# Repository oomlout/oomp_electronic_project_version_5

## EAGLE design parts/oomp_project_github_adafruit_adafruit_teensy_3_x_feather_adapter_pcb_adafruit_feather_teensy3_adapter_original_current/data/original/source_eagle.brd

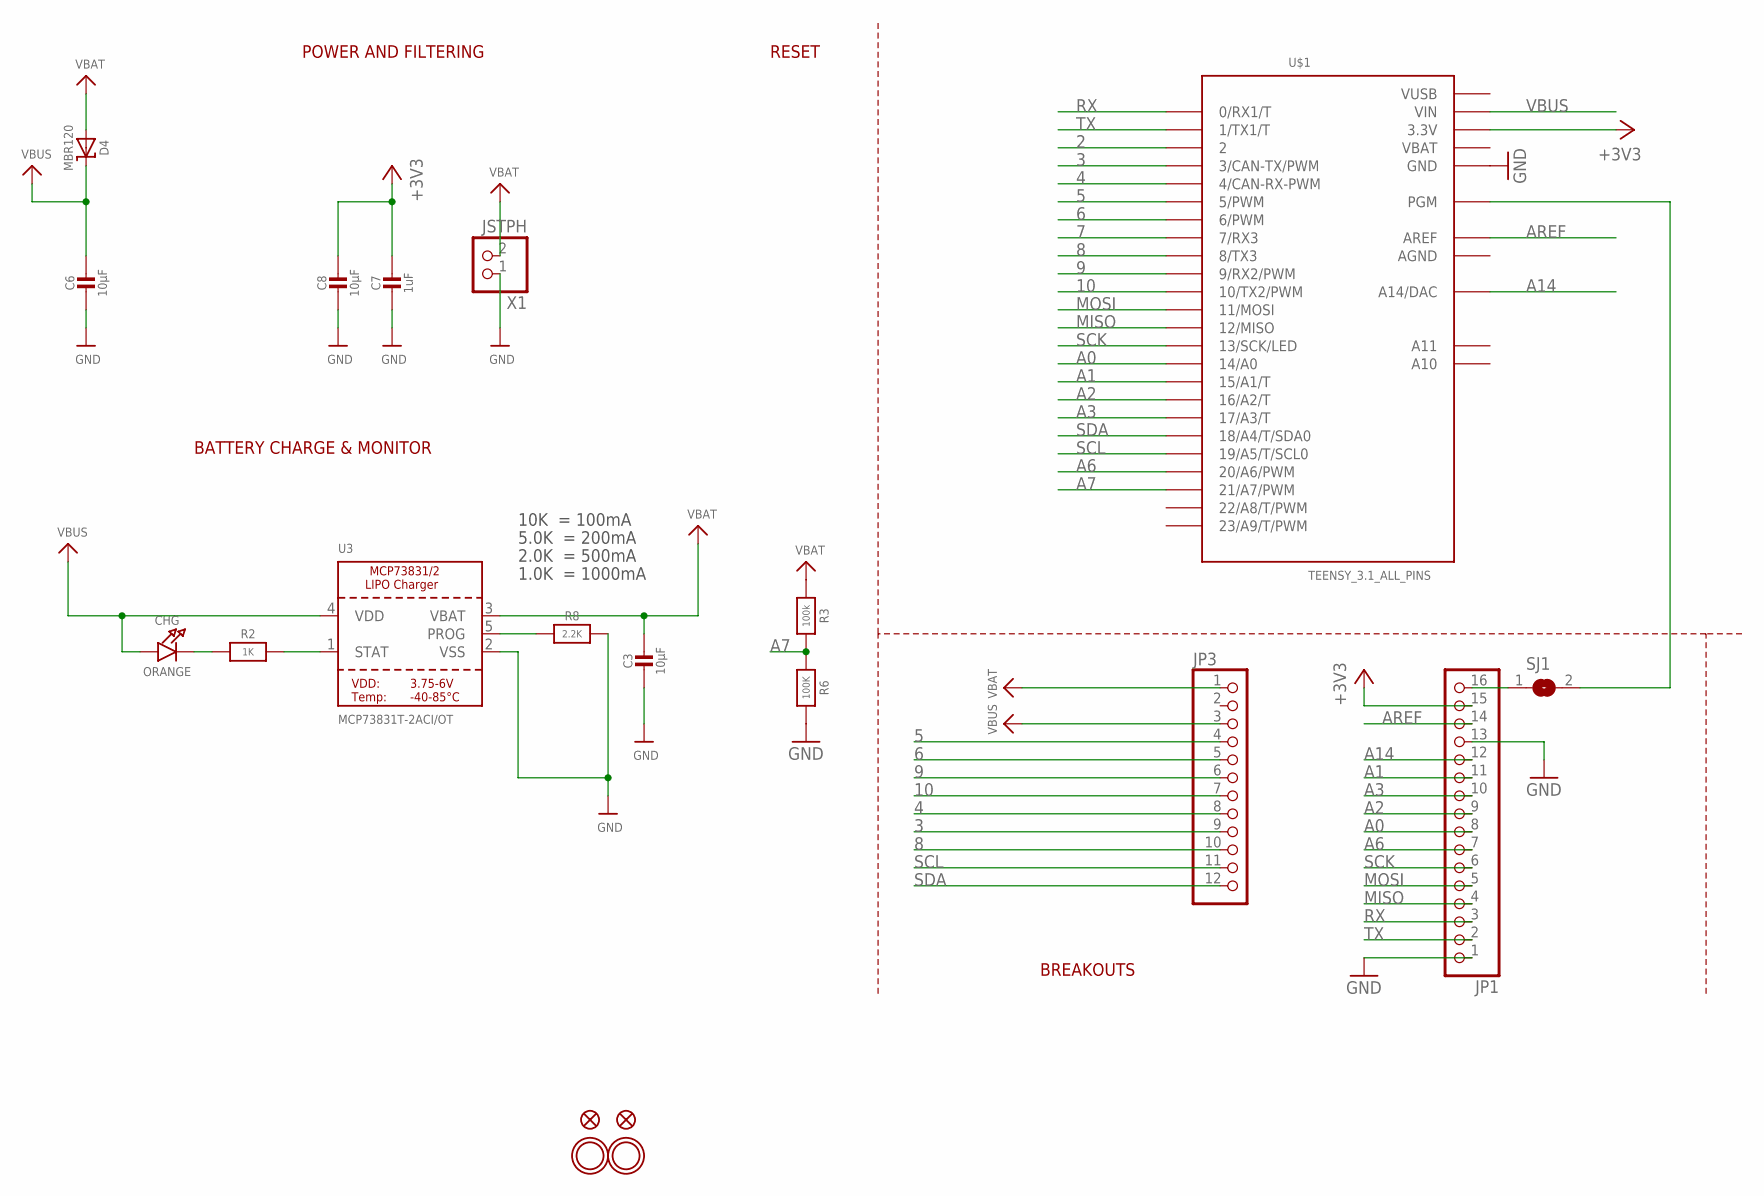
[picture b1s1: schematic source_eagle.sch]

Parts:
C3, C6, C8: 10µF; 0805-NO
C7: 1uF; 0603-NO
CHG: ORANGE; CHIPLED_0805_NOOUTLINE
D4: MBR120; SOD-123
JP1: HEADER-1X16ROUND; 1X16_ROUND
JP3: HEADER-1X12; 1X12_ROUND
R2: 1K; 0603-NO
R3: 100k; 0603-NO
R6: 100K; 0603-NO
R8: 2.2K; 0603-NO
SJ1: SOLDERJUMPERCLOSED; SOLDERJUMPER_CLOSEDWIRE
U3: MCP73831T-2ACI/OT; SOT23-5
U$1: TEENSY_3.1_ALL_PINS; TEENSY3-ALL_PINS
U$31, U$32: MOUNTINGHOLE2.5; MOUNTINGHOLE_2.5_PLATED
U$34, U$35: FIDUCIAL""; FIDUCIAL_1MM
X1: JSTPH; JSTPH2

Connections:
2: U$1.2
3: JP3.9, U$1.3 (3/CAN-TX/PWM)
4: JP3.8, U$1.4 (4/CAN-RX-PWM)
5: JP3.4, U$1.5 (5/PWM)
6: JP3.5, U$1.6 (6/PWM)
7: U$1.7 (7/RX3)
8: JP3.10, U$1.8 (8/TX3)
9: JP3.6, U$1.9 (9/RX2/PWM)
10: JP3.7, U$1.10 (10/TX2/PWM)
+3V3: C7.1, C8.1, JP1.15, U$1.3.3V, U$1.3.3V1 (3.3V)
A0: JP1.8, U$1.14/A0
A1: JP1.11, U$1.15/A1 (15/A1/T)
A2: JP1.9, U$1.16/A2 (16/A2/T)
A3: JP1.10, U$1.17/A3 (17/A3/T)
A6: JP1.7, U$1.20/A6 (20/A6/PWM)
A7: R3.2, R6.1, U$1.21/A7 (21/A7/PWM)
A14: JP1.12, U$1.RESET/DAC (A14/DAC)
AGND: U$1.AGND
AREF: JP1.14, U$1.AREF
BOOT: SJ1.2, U$1.PGM
GND: C3.2, C6.2, C7.2, C8.2, JP1.1, JP1.13, R6.2, R8.2, U3.2 (VSS), U$1.GND, U$1.GND1 (GND), X1.1
MISO: JP1.4, U$1.12 (12/MISO)
MOSI: JP1.5, U$1.11 (11/MOSI)
unnamed: CHG.C, R2.1
unnamed: R2.2, U3.1 (STAT)
unnamed: R8.1, U3.5 (PROG)
RST/BOOT: JP1.16, SJ1.1
RX: JP1.3, U$1.0 (0/RX1/T)
SCK: JP1.6, U$1.13 (13/SCK/LED)
SCL: JP3.11, U$1.19/A5 (19/A5/T/SCL0)
SDA: JP3.12, U$1.18/A4 (18/A4/T/SDA0)
TX: JP1.2, U$1.1 (1/TX1/T)
VBAT: C3.1, D4.A, JP3.1, R3.1, U3.3 (VBAT), U$1.VBAT, X1.2
VBUS: C6.1, CHG.A, D4.C, JP3.3, U3.4 (VDD), U$1.VIN
VUSB: U$1.VUSB

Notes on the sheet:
POWER AND FILTERING
RESET
10K = 100mA
5.0K = 200mA
2.0K = 500mA
1.0K = 1000mA
BATTERY CHARGE & MONITOR
BREAKOUTS

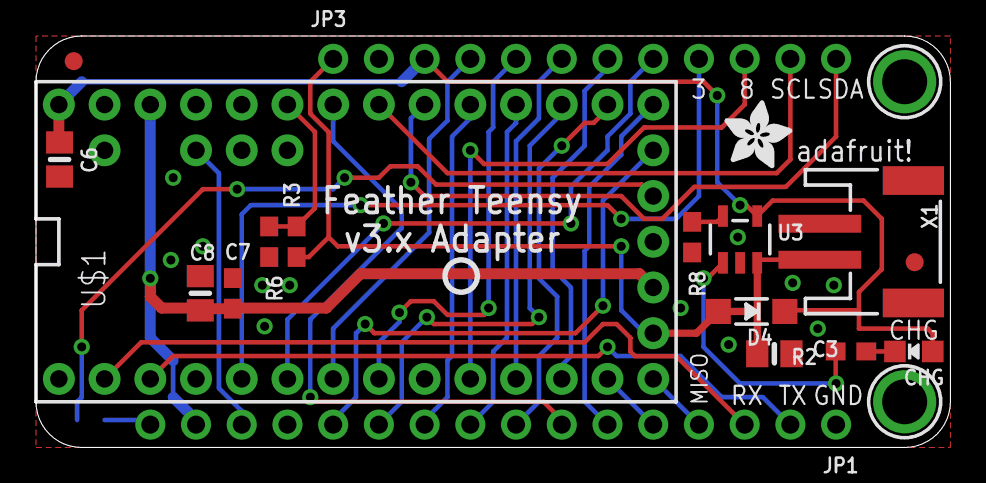
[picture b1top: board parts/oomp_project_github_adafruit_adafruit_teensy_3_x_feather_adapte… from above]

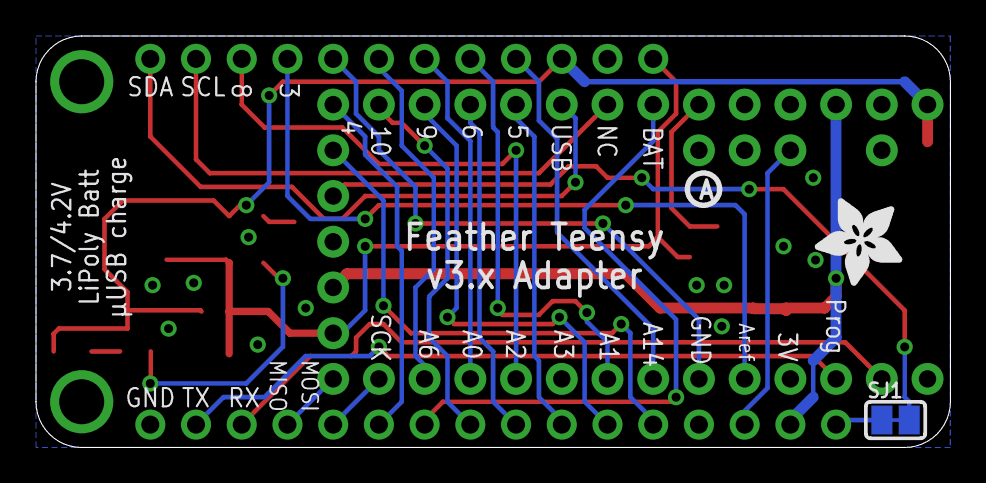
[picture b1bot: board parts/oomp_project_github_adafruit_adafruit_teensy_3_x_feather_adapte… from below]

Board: 2 copper layers, 50.8 x 22.9 mm, 24 parts (3 on the bottom side), 31 nets.

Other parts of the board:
U$4: ADAFRUIT_5MM
U$5, U$6: PCBFEAT-REV-040
U$7: ADAFRUIT_3.5MM

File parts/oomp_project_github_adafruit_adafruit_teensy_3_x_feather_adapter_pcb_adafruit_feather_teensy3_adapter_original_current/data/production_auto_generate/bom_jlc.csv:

Comment,Designator,Footprint,LCSC Part #
,JP3,Adafruit Feather Teensy3 Adapter Original-import-fps:1X12_ROUND,C7501588
,JP1,Adafruit Feather Teensy3 Adapter Original-import-fps:1X16_ROUND,C7501270
,U$7,Adafruit Feather Teensy3 Adapter Original-import-fps:ADAFRUIT_3.5MM,
,U$4,Adafruit Feather Teensy3 Adapter Original-import-fps:ADAFRUIT_5MM,
,"U$5,U$6",Adafruit Feather Teensy3 Adapter Original-import-fps:PCBFEAT-REV-040,
100k,R3,Adafruit Feather Teensy3 Adapter Original-import-fps:0603-NO,C25803
100K,R6,Adafruit Feather Teensy3 Adapter Original-import-fps:0603-NO,C25803
10µF,"C3,C6,C8",Adafruit Feather Teensy3 Adapter Original-import-fps:0805-NO,
1K,R2,Adafruit Feather Teensy3 Adapter Original-import-fps:0603-NO,C2907002
1uF,C7,Adafruit Feather Teensy3 Adapter Original-import-fps:0603-NO,C5673
2.2K,R8,Adafruit Feather Teensy3 Adapter Original-import-fps:0603-NO,C4190
"FIDUCIAL""""","U$34,U$35",Adafruit Feather Teensy3 Adapter Original-import-fps:FIDUCIAL_1MM,
JSTPH,X1,Adafruit Feather Teensy3 Adapter Original-import-fps:JSTPH2,
MBR120,D4,Adafruit Feather Teensy3 Adapter Original-import-fps:SOD-123,
MCP73831T-2ACI/OT,U3,Adafruit Feather Teensy3 Adapter Original-import-fps:SOT23-5,
ORANGE,CHG0,Adafruit Feather Teensy3 Adapter Original-import-fps:CHIPLED_0805_NOOUTLINE,
TEENSY_3.1_ALL_PINS,U$1,Adafruit Feather Teensy3 Adapter Original-import-fps:TEENSY3-ALL_PINS,

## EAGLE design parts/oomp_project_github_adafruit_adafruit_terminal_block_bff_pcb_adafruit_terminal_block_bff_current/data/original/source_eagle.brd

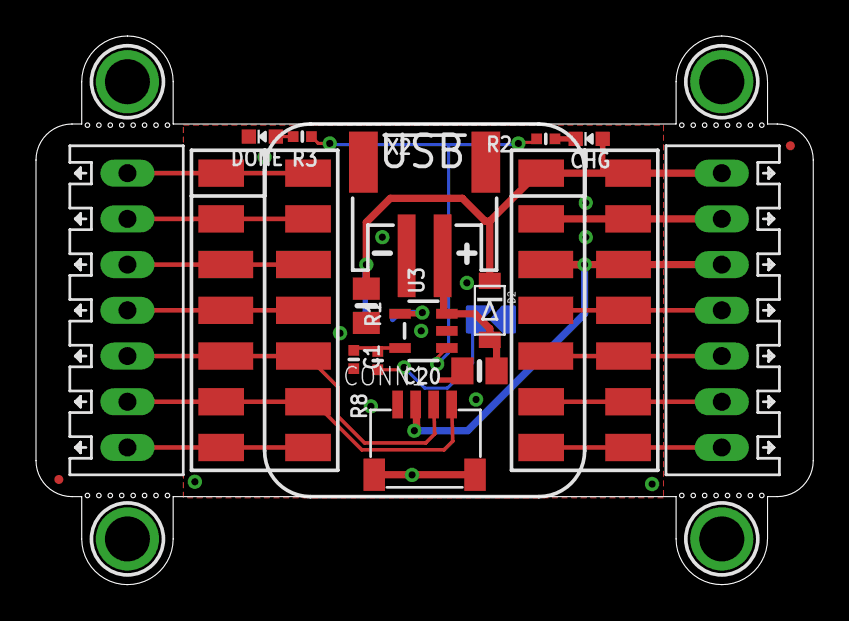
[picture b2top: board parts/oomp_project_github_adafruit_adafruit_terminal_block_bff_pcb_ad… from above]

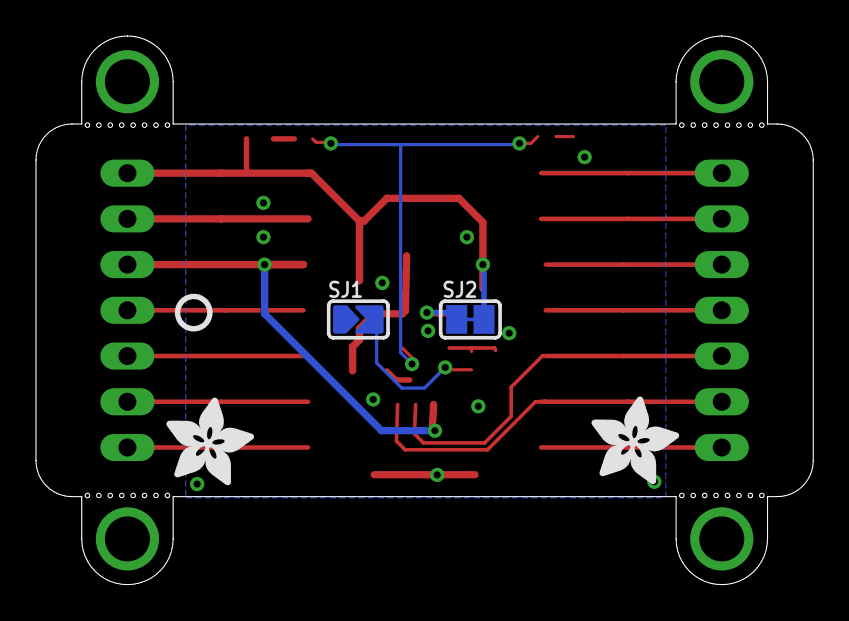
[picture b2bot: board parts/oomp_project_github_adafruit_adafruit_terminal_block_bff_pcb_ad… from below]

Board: 2 copper layers, 43.2 x 30.5 mm, 64 parts (26 on the bottom side), 21 nets.

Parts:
C1, C20: 10uF; 0805-NO
CHG: ORANGE; CHIPLED_0603_NOOUTLINE
CONN1: STEMMA_I2C_QT; JST_SH4
D2: PMEG2020; SOD-123FL
DONE: GREEN; CHIPLED_0603_NOOUTLINE
FID1, FID2: FIDUCIAL_0.5MM
JP1, JP2: Terminal; 1X07_2.54MMTERMINAL
PLABEL0: PLABEL0
PLABEL1: PLABEL1
PLABEL2: PLABEL2
PLABEL3: PLABEL3
PLABEL4: PLABEL4
PLABEL5: PLABEL5
PLABEL6: PLABEL6
PLABEL7: PLABEL7
PLABEL8: PLABEL8
PLABEL9: PLABEL9
PLABEL10: PLABEL10
PLABEL11: PLABEL11
PLABEL12: PLABEL12
PLABEL13: PLABEL13
PLABEL14: PLABEL14
PLABEL15: PLABEL15
PLABEL16: PLABEL16
PLABEL17: PLABEL17
PLABEL18: PLABEL18
PLABEL19: PLABEL19
PLABEL20: PLABEL20
PLABEL21: PLABEL21
PLABEL22: PLABEL22
PLABEL23: PLABEL23
PLABEL24: PLABEL24
PLABEL25: PLABEL25
PLABEL26: PLABEL26
PLABEL27: PLABEL27
PLABEL28: PLABEL28
PLABEL29: PLABEL29
PLABEL31: PLABEL31
PLABEL32: PLABEL32
PLABEL33: PLABEL33
PLABEL34: PLABEL34
PLABEL35: PLABEL35
PLABEL36: PLABEL36
PLABEL37: PLABEL37
PLABEL38: PLABEL38
R1, R2, R3, R8: 5.1K; _0402NO
SJ1: SOLDERJUMPER_ARROW_NOPASTE
SJ2: SOLDERJUMPER_CLOSEDWIRE
U3: MCP73831T-2ACI/OT; SOT23-5
U$1, U$2, U$3, U$4: MOUNTINGHOLE2.5; MOUNTINGHOLE_2.5_PLATED
U$7, U$8: ADAFRUIT_5MM
U$9: PCBFEAT-REV-040
X1: QTPY_SOCKET_DUAL_SMT; QTPY_SMT
X2: JSTPH; JSTPH2_BATT

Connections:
3.3V: CONN1.2, JP1.5, X1.12, X1.12B
+5V: C1.1, CHG.A, D2.C, JP1.7, SJ2.2, X1.14, X1.14B
A0: JP2.1, X1.1, X1.1B
A1: JP2.2, X1.2, X1.2B
A2: JP2.3, X1.3, X1.3B
A3: JP2.4, X1.4, X1.4B
GND: C1.2, C20.2, CONN1.1, CONN1.MT1, CONN1.MT2, DONE.C, JP1.6, R8.2, SJ1.1, U3.2, X1.13, X1.13B, X2.1, X2.NC1, X2.NC2
MISO: JP1.3, X1.10, X1.10B
MOSI: JP1.4, X1.11, X1.11B
unnamed: R1.1, SJ1.2
unnamed: CHG.C, R2.1
unnamed: R2.2, R3.1, U3.1
unnamed: R1.2, R8.1, U3.5
unnamed: DONE.A, R3.2
unnamed: SJ2.1, U3.4
RX: JP1.1, X1.8, X1.8B
SCK: JP1.2, X1.9, X1.9B
SCL: CONN1.4, JP2.6, X1.6, X1.6B
SDA: CONN1.3, JP2.5, X1.5, X1.5B
TX: JP2.7, X1.7, X1.7B
VBAT: C20.1, D2.A, U3.3, X2.2

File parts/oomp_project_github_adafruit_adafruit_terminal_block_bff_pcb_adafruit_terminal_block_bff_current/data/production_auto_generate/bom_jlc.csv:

Comment,Designator,Footprint,LCSC Part #
,"U$7,U$8",Adafruit Terminal Block BFF-import-fps:ADAFRUIT_5MM,
,U$9,Adafruit Terminal Block BFF-import-fps:PCBFEAT-REV-040,
,PLABEL0,Adafruit Terminal Block BFF-import-fps:PLABEL0,
,PLABEL1,Adafruit Terminal Block BFF-import-fps:PLABEL1,
,PLABEL10,Adafruit Terminal Block BFF-import-fps:PLABEL10,
,PLABEL11,Adafruit Terminal Block BFF-import-fps:PLABEL11,
,PLABEL12,Adafruit Terminal Block BFF-import-fps:PLABEL12,
,PLABEL13,Adafruit Terminal Block BFF-import-fps:PLABEL13,
,PLABEL14,Adafruit Terminal Block BFF-import-fps:PLABEL14,
,PLABEL15,Adafruit Terminal Block BFF-import-fps:PLABEL15,
,PLABEL16,Adafruit Terminal Block BFF-import-fps:PLABEL16,
,PLABEL17,Adafruit Terminal Block BFF-import-fps:PLABEL17,
,PLABEL18,Adafruit Terminal Block BFF-import-fps:PLABEL18,
,PLABEL19,Adafruit Terminal Block BFF-import-fps:PLABEL19,
,PLABEL2,Adafruit Terminal Block BFF-import-fps:PLABEL2,
,PLABEL20,Adafruit Terminal Block BFF-import-fps:PLABEL20,
,PLABEL21,Adafruit Terminal Block BFF-import-fps:PLABEL21,
,PLABEL22,Adafruit Terminal Block BFF-import-fps:PLABEL22,
,PLABEL23,Adafruit Terminal Block BFF-import-fps:PLABEL23,
,PLABEL24,Adafruit Terminal Block BFF-import-fps:PLABEL24,
,PLABEL25,Adafruit Terminal Block BFF-import-fps:PLABEL25,
,PLABEL26,Adafruit Terminal Block BFF-import-fps:PLABEL26,
,PLABEL27,Adafruit Terminal Block BFF-import-fps:PLABEL27,
,PLABEL28,Adafruit Terminal Block BFF-import-fps:PLABEL28,
,PLABEL29,Adafruit Terminal Block BFF-import-fps:PLABEL29,
,PLABEL3,Adafruit Terminal Block BFF-import-fps:PLABEL3,
,PLABEL31,Adafruit Terminal Block BFF-import-fps:PLABEL31,
,PLABEL32,Adafruit Terminal Block BFF-import-fps:PLABEL32,
,PLABEL33,Adafruit Terminal Block BFF-import-fps:PLABEL33,
,PLABEL34,Adafruit Terminal Block BFF-import-fps:PLABEL34,
,PLABEL35,Adafruit Terminal Block BFF-import-fps:PLABEL35,
,PLABEL36,Adafruit Terminal Block BFF-import-fps:PLABEL36,
,PLABEL37,Adafruit Terminal Block BFF-import-fps:PLABEL37,
,PLABEL38,Adafruit Terminal Block BFF-import-fps:PLABEL38,
,PLABEL4,Adafruit Terminal Block BFF-import-fps:PLABEL4,
,PLABEL5,Adafruit Terminal Block BFF-import-fps:PLABEL5,
,PLABEL6,Adafruit Terminal Block BFF-import-fps:PLABEL6,
,PLABEL7,Adafruit Terminal Block BFF-import-fps:PLABEL7,
,PLABEL8,Adafruit Terminal Block BFF-import-fps:PLABEL8,
,PLABEL9,Adafruit Terminal Block BFF-import-fps:PLABEL9,
10uF,"C1,C20",Adafruit Terminal Block BFF-import-fps:0805-NO,
5.1K,"R1,R2,R3,R8",Adafruit Terminal Block BFF-import-fps:_0402NO,C25905
GREEN,DONE0,Adafruit Terminal Block BFF-import-fps:CHIPLED_0603_NOOUTLINE,
JSTPH,X2,Adafruit Terminal Block BFF-import-fps:JSTPH2_BATT,
MCP73831T-2ACI/OT,U3,Adafruit Terminal Block BFF-import-fps:SOT23-5,
ORANGE,CHG0,Adafruit Terminal Block BFF-import-fps:CHIPLED_0603_NOOUTLINE,
PMEG2020,D2,Adafruit Terminal Block BFF-import-fps:SOD-123FL,
QTPY_SOCKET_DUAL_SMT,X1,Adafruit Terminal Block BFF-import-fps:QTPY_SMT,
STEMMA_I2C_QT,CONN1,Adafruit Terminal Block BFF-import-fps:JST_SH4,C160404
Terminal,"JP1,JP2",Adafruit Terminal Block BFF-import-fps:1X07_2.54MMTERMINAL,C7501585

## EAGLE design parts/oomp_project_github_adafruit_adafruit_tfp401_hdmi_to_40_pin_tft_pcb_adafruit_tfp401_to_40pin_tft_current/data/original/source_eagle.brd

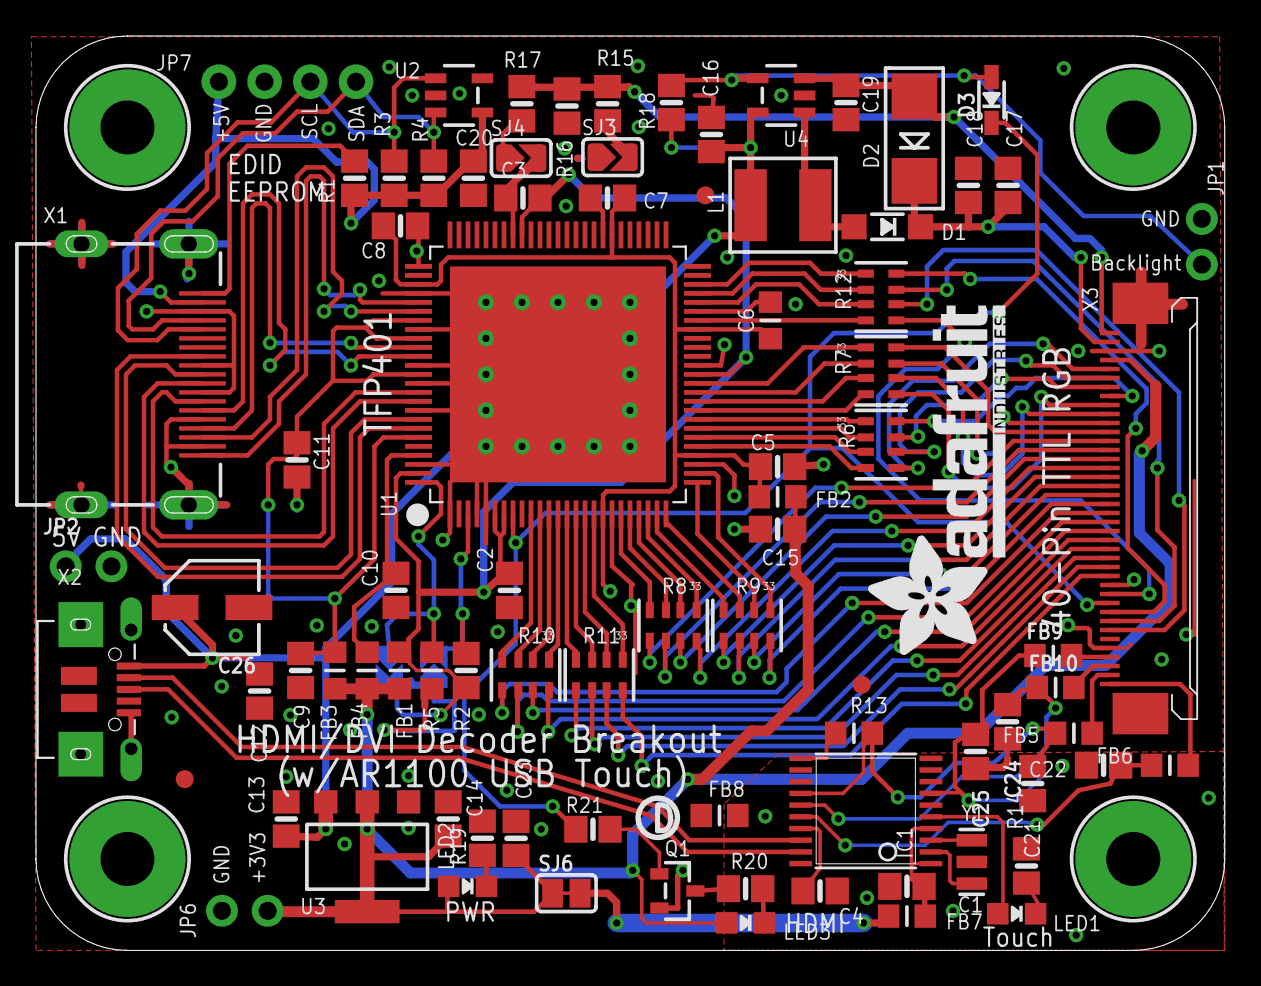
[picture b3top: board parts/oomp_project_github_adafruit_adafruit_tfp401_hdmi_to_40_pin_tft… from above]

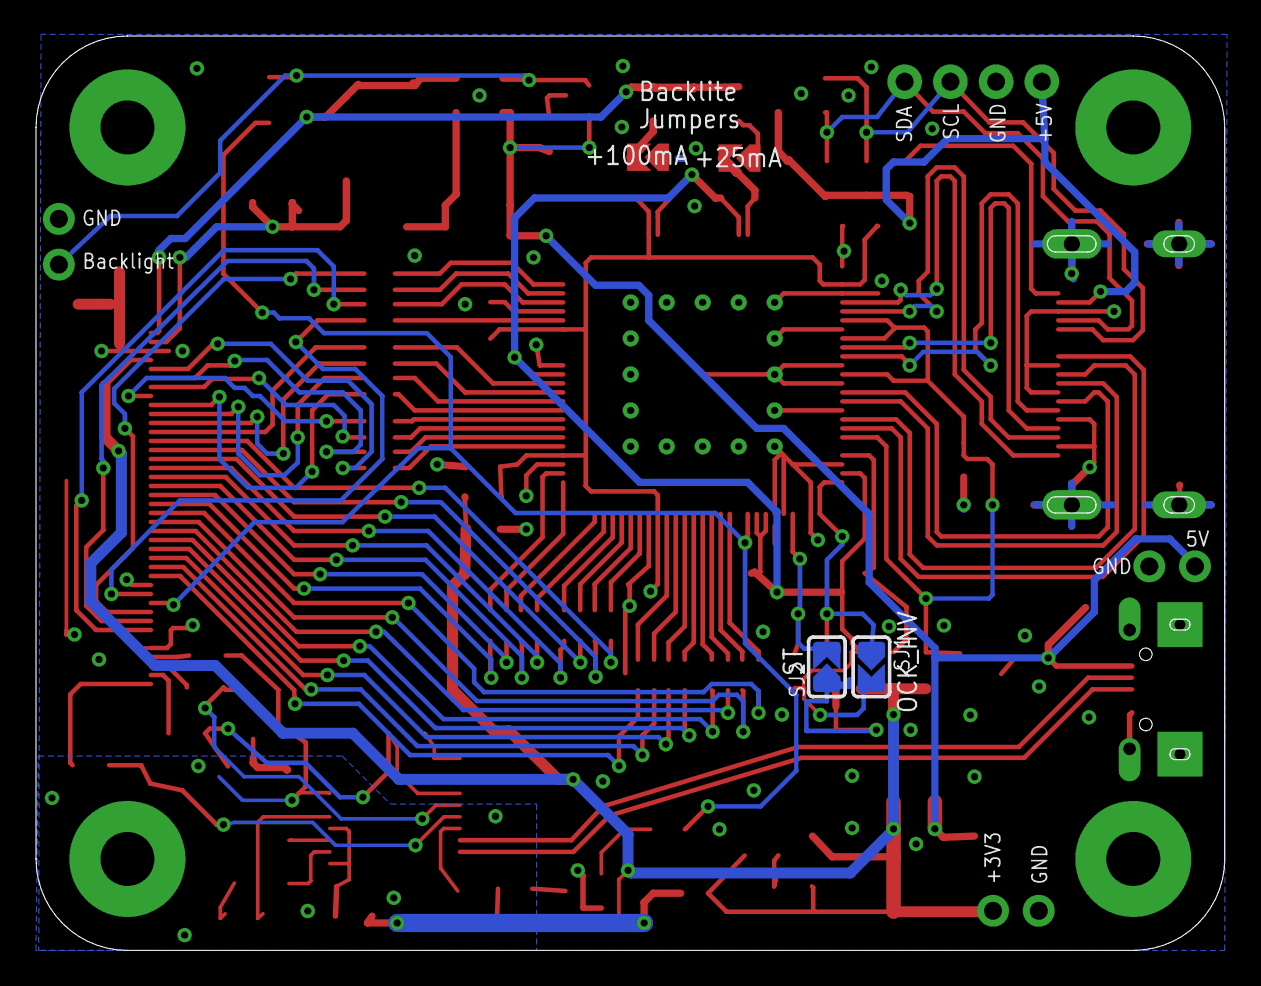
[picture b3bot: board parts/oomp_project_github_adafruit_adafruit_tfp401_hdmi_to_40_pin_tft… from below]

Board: 2 copper layers, 66.0 x 50.8 mm, 92 parts (2 on the bottom side), 107 nets.

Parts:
C1, C2, C3, C4, C5, C7, C8, C9, C10, C11, C19, C20, C23: 0.1uF; 0805-NO
C6: 0.1uF; _0805MP
C12, C13, C14, C15, C16: 10uF; 0805-NO
C17, C18: 1uF; 0805-NO
C21, C22, C24, C25: 0.01uF; 0805-NO
C26: 100uF; PANASONIC_C
D1: MBR0540; SOD-123
D2: MM3Z24VT1G; SMADIODE
D3: 2N4148; SOD-323
FB1, FB2, FB3, FB4, FB7, FB8: Ferrite; _0805MP
FB5, FB6, FB9, FB10: ferrite; _0805MP
FID1, FID2, FID3: FIDUCIAL""; FIDUCIAL_1MM
IC1: AR1100_SSOP; TSSOP20-5.3MMBODY
JP1, JP2, JP6: 1X02_ROUND
JP7: 1X04_ROUND_76
L1: BRL3225T150K; INDUCTOR_5X5MM_NR5040_NOTHERMALS
LED1: Red; CHIPLED_0805_NOOUTLINE
LED2: Green; CHIPLED_0805_NOOUTLINE
LED3: Blue; CHIPLED_0805_NOOUTLINE
Q1: BSS138; SOT23-R
R1, R2, R3, R4, R18: 10K; 0805-NO
R5, R13: 10K; _0805MP
R6, R7, R8, R9, R10, R11, R12: 33; RESPACK_4X0603
R14, R19, R20, R21: 1K; 0805-NO
R15: 3 ohm; 0805-NO
R16, R17: 12 ohm; 0805-NO
SJ1, SJ2: SOLDERJUMPER_ARROW_NOPASTE
SJ3: +50mA; SOLDERJUMPER_ARROW_NOPASTE
SJ4: +25mA; SOLDERJUMPER_ARROW_NOPASTE
SJ6: SOLDERJUMPER_CLOSEDWIRE
U1: TFP401; S-PQFP-G100
U2: 24LC02BT-I/OT; SOT23-5
U3: LT1117(3V3); SOT223-R
U4: FAN5333BSX; SOT23-5
U$31, U$32, U$33, U$34: MOUNTINGHOLE3.0; MOUNTINGHOLE_3.0_PLATED
U$80: PCBFEAT-REV-056
U$81: ADAFRUIT_TEXT_20MM
X1: 47151-0001; HDMI_MOLEX_47151-0001_DIMLAYER
X2: microUSB; 4UCONN_20329
X3: XF2-40-RARBT; 4-1734839-0
Y1: 12MHz; RESONATOR-SMD

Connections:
5.0V: C20.1, JP7.1, R1.2, R3.2, R4.2, U2.4, X1.18
24V: C17.1, C18.1, D1.C, D2.C, X3.2
ACTIVE: D3.C, R21.1, U1.8, X3.31
AGND: C1.1, C4.2, C21.2, C22.2, C24.2, C25.2, FB8.2, IC1.6, IC1.8, IC1.9, IC1.13, IC1.20, R14.2, Y1.2
ASD: R12.3, U1.46
AVDD: C9.1, C11.1, FB3.2, U1.82, U1.84, U1.88, U1.95
AVDD2: FB7.2, SJ6.2
B0: R10.4, U1.10
B1: R10.3, U1.11
B2: R10.2, U1.12
B3: R10.1, U1.13
B4: R11.4, U1.14
B5: R11.3, U1.15
B6: R11.2, U1.16
B7: R11.1, U1.17
CVB: R12.2, U1.47
D+: IC1.19, X2.D+
D-: IC1.18, X2.D-
DISPEN: R12.6, X3.34
G0: R8.4, U1.20
G1: R8.3, U1.21
G2: R8.2, U1.22
G3: R8.1, U1.23
G4: R9.4, U1.24
G5: R9.3, U1.25
G6: R9.2, U1.26
G7: R9.1, U1.27
GND: C2.2, C3.2, C5.2, C6.2, C7.2, C8.2, C9.2, C10.2, C11.2, C12.2, C13.2, C14.2, C15.2, C16.1, C17.2, C18.2, C19.2, C20.2, C23.2, C26.-, FB8.1, JP1.1, JP2.2, JP6.2, JP7.2, Q1.2, R5.1, R16.2, R19.2, SJ2.1, SJ3.1, SJ4.2, U1.1, U1.4, U1.5, U1.19, U1.28, U1.39, U1.45, U1.58, U1.68, U1.76, U1.79, U1.83, U1.87, U1.89, U1.92, U1.98, U1.P$1, U1.P$2, U1.P$3, U1.P$4, U1.P$5, U1.P$6, U1.P$7, U1.P$8, U1.P$9, U1.P$10, U1.P$11, U1.P$12, U1.P$13, U1.P$14, U1.P$15, U1.P$16, U1.THERMAL, U2.2, U2.5, U3.1, U4.2, X1.2, X1.5, X1.8, X1.11, X1.17, X1.P$1, X1.P$2, X1.P$3, X1.P$4, X2.BASE@1, X2.BASE@2, X2.GND, X2.SPRT@1, X2.SPRT@2, X2.SPRT@3, X2.SPRT@4, X3.3, X3.29, X3.36
HSYNC: R12.8, X3.32
LEDK: C19.1, D2.A, R15.1, R16.1, R17.1, U4.3, X3.1
unnamed: U1.93, X1.10
unnamed: U1.94, X1.12
unnamed: U1.90, X1.7
unnamed: U1.91, X1.9
unnamed: U1.85, X1.4
unnamed: U1.86, X1.6
unnamed: U1.80, X1.1
unnamed: U1.81, X1.3
unnamed: R1.1, X1.19
unnamed: IC1.2, Y1.1
unnamed: IC1.3, Y1.3
unnamed: C4.1, IC1.17
unnamed: LED2.C, R19.1
unnamed: R6.5, X3.5
unnamed: R6.6, X3.6
unnamed: R6.7, X3.7
unnamed: R6.8, X3.8
unnamed: R7.5, X3.9
unnamed: R7.6, X3.10
unnamed: R7.7, X3.11
unnamed: R7.8, X3.12
unnamed: R8.5, X3.13
unnamed: R8.6, X3.14
unnamed: R8.7, X3.15
unnamed: R8.8, X3.16
unnamed: R9.5, X3.17
unnamed: R9.6, X3.18
unnamed: R9.7, X3.19
unnamed: R9.8, X3.20
unnamed: R10.5, X3.21
unnamed: R10.6, X3.22
unnamed: R10.7, X3.23
unnamed: R10.8, X3.24
unnamed: R11.5, X3.25
unnamed: R11.6, X3.26
unnamed: R11.7, X3.27
unnamed: C10.1, FB4.2, U1.97
unnamed: R11.8, X3.28
unnamed: IC1.11, R13.2
unnamed: LED1.C, R14.1
unnamed: C5.1, C6.1, C7.1, C8.1, FB2.2, U1.18, U1.29, U1.43, U1.57, U1.78
unnamed: IC1.5, LED1.A
unnamed: LED3.C, R20.1
unnamed: Q1.3, R20.2
unnamed: D1.A, L1.P$2, U4.1
unnamed: Q1.1, R21.2
unnamed: R15.2, SJ3.2
unnamed: R17.2, SJ4.1
unnamed: D3.A, JP1.2, R18.2, U4.4
unnamed: FB5.2, X3.39
unnamed: FB6.2, X3.40
unnamed: C1.2, FB7.1, IC1.1, IC1.4
unnamed: FB9.2, X3.37
unnamed: FB10.2, X3.38
OCK_INV: R5.2, SJ1.1, U1.100
PIXCLK: R12.5, X3.30
R0: R6.4, U1.30
R1: R6.3, U1.31
R2: R6.2, U1.32
R3: R6.1, U1.33
R4: R7.4, U1.34
R5: R7.3, U1.35
R6: R7.2, U1.36
R7: R7.1, U1.37
SCL: JP7.3, R3.1, U2.1, X1.15
SDA: JP7.4, R4.1, U2.3, X1.16
ST: R2.2, SJ2.2, U1.3
VDD: C14.1, C15.1, C23.1, FB1.1, FB2.1, FB3.1, FB4.1, JP6.1, LED2.A, LED3.A, SJ6.1, U3.2, U3.4, X3.4
VDDIO: C2.1, C3.1, FB1.2, R2.1, SJ1.2, U1.6, U1.7, U1.38, U1.67, U1.99
VIN: C12.1, C13.1, C16.2, C26.+, JP2.1, L1.P$1, R18.1, U3.3, U4.5, X2.VBUS
VSYNC: R12.7, X3.33
X+: C25.1, FB9.1, IC1.7
X-: C21.1, FB5.1, IC1.14, R13.1
XCV: R12.1, U1.48
Y+: C24.1, FB10.1, IC1.15
Y-: C22.1, FB6.1, IC1.16
ZXC: R12.4, U1.44

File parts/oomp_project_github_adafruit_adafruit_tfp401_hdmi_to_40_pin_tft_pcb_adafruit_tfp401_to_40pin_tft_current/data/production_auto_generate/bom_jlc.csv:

Comment,Designator,Footprint,LCSC Part #
,"JP1,JP2,JP6",Adafruit TFP401 to 40pin TFT-import-fps:1X02_ROUND,C492401
,JP7,Adafruit TFP401 to 40pin TFT-import-fps:1X04_ROUND_76,C42431795
,U$81,Adafruit TFP401 to 40pin TFT-import-fps:ADAFRUIT_TEXT_20MM,
,U$80,Adafruit TFP401 to 40pin TFT-import-fps:PCBFEAT-REV-056,
0.01uF,"C21,C22,C24,C25",Adafruit TFP401 to 40pin TFT-import-fps:0805-NO,
0.1uF,"C1,C2,C3,C4,C5,C7,C8,C9,C10,C11,C19,C20,C23",Adafruit TFP401 to 40pin TFT-import-fps:0805-NO,
0.1uF,C6,Adafruit TFP401 to 40pin TFT-import-fps:_0805MP,
100uF,C26,Adafruit TFP401 to 40pin TFT-import-fps:PANASONIC_C,
10K,"R1,R2,R3,R4,R18",Adafruit TFP401 to 40pin TFT-import-fps:0805-NO,C17414
10K,"R5,R13",Adafruit TFP401 to 40pin TFT-import-fps:_0805MP,C17414
10uF,"C12,C13,C14,C15,C16",Adafruit TFP401 to 40pin TFT-import-fps:0805-NO,
12 ohm,"R16,R17",Adafruit TFP401 to 40pin TFT-import-fps:0805-NO,C2907226
12MHz,Y1,Adafruit TFP401 to 40pin TFT-import-fps:RESONATOR-SMD,
1K,"R14,R19,R20,R21",Adafruit TFP401 to 40pin TFT-import-fps:0805-NO,C17513
1uF,"C17,C18",Adafruit TFP401 to 40pin TFT-import-fps:0805-NO,
24LC02BT-I/OT,U2,Adafruit TFP401 to 40pin TFT-import-fps:SOT23-5,
2N4148,D3,Adafruit TFP401 to 40pin TFT-import-fps:SOD-323,
3 ohm,R15,Adafruit TFP401 to 40pin TFT-import-fps:0805-NO,
33,"R6,R7,R8,R9,R10,R11,R12",Adafruit TFP401 to 40pin TFT-import-fps:RESPACK_4X0603,C23140
47151-0001,X1,Adafruit TFP401 to 40pin TFT-import-fps:HDMI_MOLEX_47151-0001_DIMLAYER,
AR1100_SSOP,IC1,Adafruit TFP401 to 40pin TFT-import-fps:TSSOP20-5.3MMBODY,
Blue,LED3,Adafruit TFP401 to 40pin TFT-import-fps:CHIPLED_0805_NOOUTLINE,
BRL3225T150K,L1,Adafruit TFP401 to 40pin TFT-import-fps:INDUCTOR_5X5MM_NR5040_NOTHERMALS,
BSS138,Q1,Adafruit TFP401 to 40pin TFT-import-fps:SOT23-R,C52895
FAN5333BSX,U4,Adafruit TFP401 to 40pin TFT-import-fps:SOT23-5,
Ferrite,"FB1,FB2,FB3,FB4,FB7,FB8",Adafruit TFP401 to 40pin TFT-import-fps:_0805MP,
ferrite,"FB5,FB6,FB9,FB10",Adafruit TFP401 to 40pin TFT-import-fps:_0805MP,
Green,LED2,Adafruit TFP401 to 40pin TFT-import-fps:CHIPLED_0805_NOOUTLINE,
LT1117(3V3),U3,Adafruit TFP401 to 40pin TFT-import-fps:SOT223-R,
MBR0540,D1,Adafruit TFP401 to 40pin TFT-import-fps:SOD-123,
microUSB,X2,Adafruit TFP401 to 40pin TFT-import-fps:4UCONN_20329,
MM3Z24VT1G,D2,Adafruit TFP401 to 40pin TFT-import-fps:SMADIODE,
Red,LED1,Adafruit TFP401 to 40pin TFT-import-fps:CHIPLED_0805_NOOUTLINE,
TFP401,U1,Adafruit TFP401 to 40pin TFT-import-fps:S-PQFP-G100,
XF2-40-RARBT,X3,Adafruit TFP401 to 40pin TFT-import-fps:4-1734839-0,

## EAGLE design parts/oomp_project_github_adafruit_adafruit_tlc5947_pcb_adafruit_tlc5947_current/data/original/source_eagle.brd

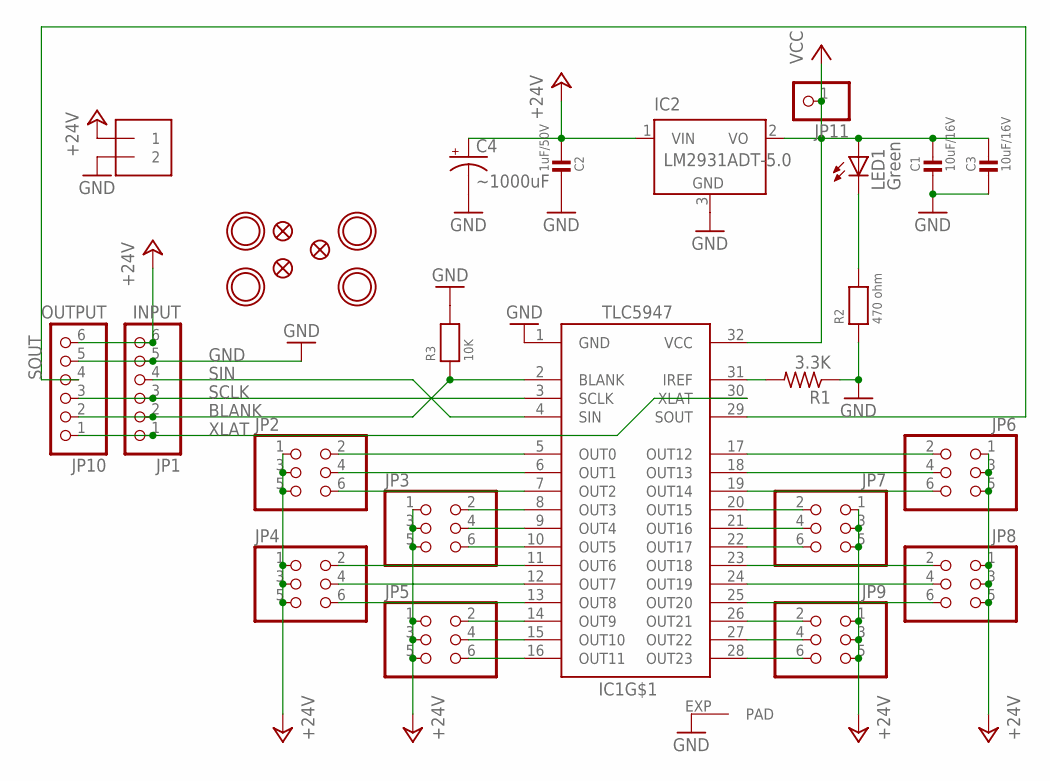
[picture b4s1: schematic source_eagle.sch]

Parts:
C1, C3: 10uF/16V; 0805
C2: 1uF/50V; 0805
C4: ~1000uF; E3,5-8
FID1, FID2, FID3: FIDUCIAL""; FIDUCIAL_1MM
IC1: TLC5947-DAP; HTSSOP32DAP
IC2: LM2931ADT-5.0; TO252
J1: 1X2-3.5MM
JP1: INPUT; 1X06-CLEANBIG
JP2, JP3, JP4, JP5, JP6, JP7, JP8, JP9: HEADER-2X3; 2X03_ROUND_70MIL
JP10: OUTPUT; 1X06-CLEANBIG
JP11: PINHD-1X1CB; 1X01-CLEANBIG
LED1: Green; CHIP-LED0805
R1: 3.3K; 0805-THM
R2: 470 ohm; 0805
R3: 10K; 0805
U$1, U$2, U$3, U$4: MOUNTINGHOLE2.5; MOUNTINGHOLE_2.5_PLATED

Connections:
+24V: C2.1, C4.+, IC2.1 (VIN), J1.1, JP1.6, JP2.1, JP2.3, JP2.5, JP3.1, JP3.3, JP3.5, JP4.1, JP4.3, JP4.5, JP5.1, JP5.3, JP5.5, JP6.1, JP6.3, JP6.5, JP7.1, JP7.3, JP7.5, JP8.1, JP8.3, JP8.5, JP9.1, JP9.3, JP9.5, JP10.6
BLANK: IC1.2 (BLANK), JP1.2, JP10.2, R3.1
GND: C1.2, C2.2, C3.2, C4.-, IC1.1 (GND), IC1.EXP (PAD), IC2.3 (GND), J1.2, JP1.5, JP10.5, R1.1, R2.1, R3.2
unnamed: LED1.C, R2.2
unnamed: IC1.31 (IREF), R1.2
unnamed: IC1.5 (OUT0), JP2.2
unnamed: IC1.6 (OUT1), JP2.4
unnamed: IC1.7 (OUT2), JP2.6
unnamed: IC1.8 (OUT3), JP3.2
unnamed: IC1.9 (OUT4), JP3.4
unnamed: IC1.10 (OUT5), JP3.6
unnamed: IC1.11 (OUT6), JP4.2
unnamed: IC1.12 (OUT7), JP4.4
unnamed: IC1.13 (OUT8), JP4.6
unnamed: IC1.14 (OUT9), JP5.2
unnamed: IC1.15 (OUT10), JP5.4
unnamed: IC1.16 (OUT11), JP5.6
unnamed: IC1.26 (OUT21), JP9.2
unnamed: IC1.27 (OUT22), JP9.4
unnamed: IC1.28 (OUT23), JP9.6
unnamed: IC1.23 (OUT18), JP8.2
unnamed: IC1.24 (OUT19), JP8.4
unnamed: IC1.25 (OUT20), JP8.6
unnamed: IC1.20 (OUT15), JP7.2
unnamed: IC1.21 (OUT16), JP7.4
unnamed: IC1.22 (OUT17), JP7.6
unnamed: IC1.17 (OUT12), JP6.2
unnamed: IC1.18 (OUT13), JP6.4
unnamed: IC1.19 (OUT14), JP6.6
SCLK: IC1.3 (SCLK), JP1.3, JP10.3
SIN: IC1.4 (SIN), JP1.4
SOUT: IC1.29 (SOUT), JP10.4
VCC: C1.1, C3.1, IC1.32 (VCC), IC2.2 (VO), JP11.1, LED1.A
XLAT: IC1.30 (XLAT), JP1.1, JP10.1

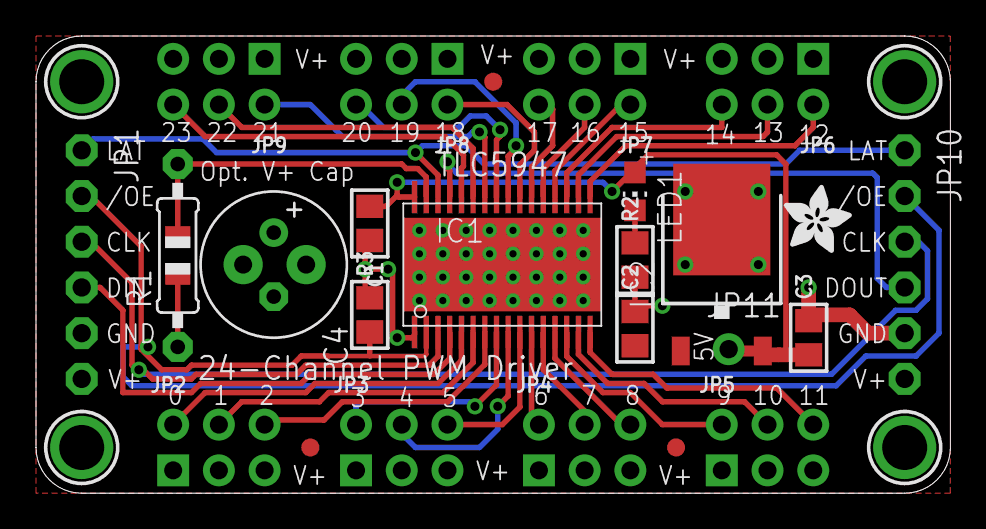
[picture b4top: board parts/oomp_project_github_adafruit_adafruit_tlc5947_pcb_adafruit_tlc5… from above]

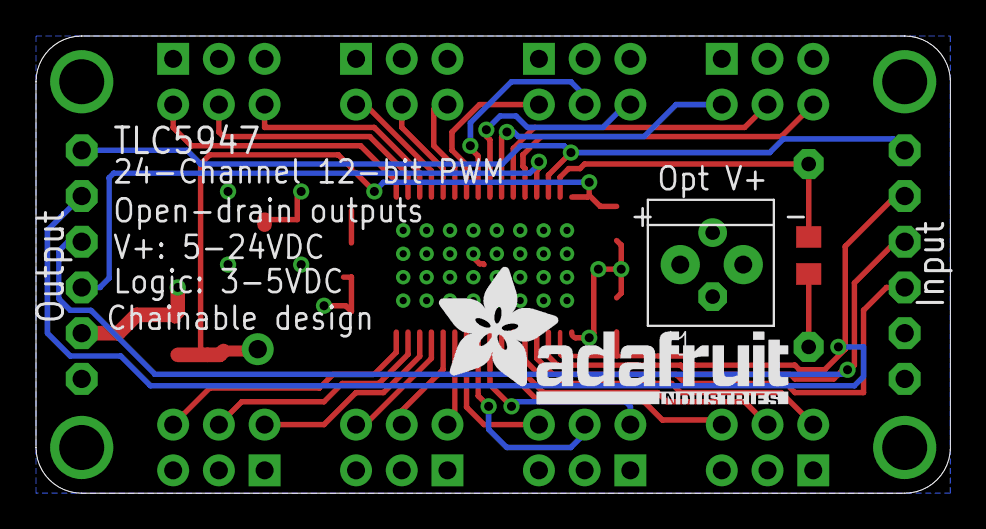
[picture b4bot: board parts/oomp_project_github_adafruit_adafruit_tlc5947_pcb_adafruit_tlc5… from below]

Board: 2 copper layers, 50.8 x 25.4 mm, 31 parts (2 on the bottom side), 34 nets.

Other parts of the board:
U$5: ADAFRUIT_TEXT_20MM
U$6: ADAFRUIT_3.5MM

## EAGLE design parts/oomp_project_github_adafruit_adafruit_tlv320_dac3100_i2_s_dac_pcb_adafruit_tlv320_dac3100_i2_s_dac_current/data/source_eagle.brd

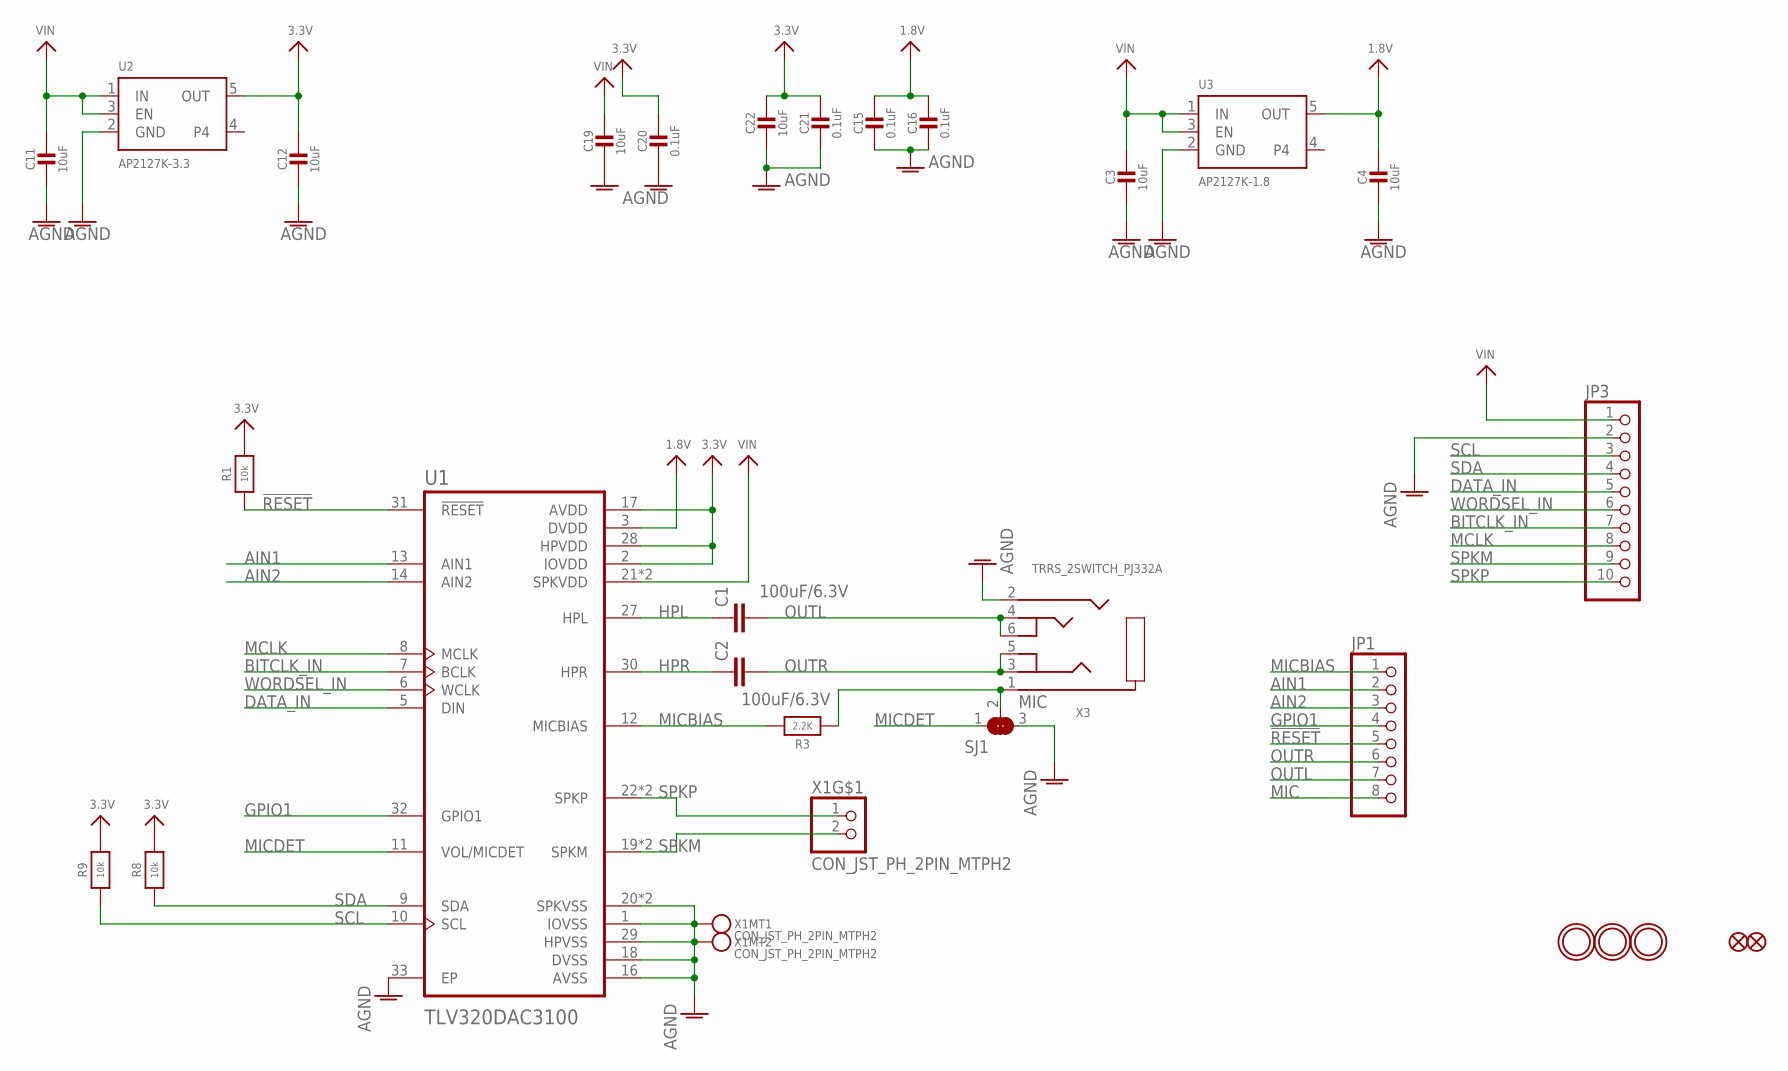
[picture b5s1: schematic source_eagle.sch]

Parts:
C1, C2: 100uF/6.3V; C1210
C3, C4, C11, C12, C19, C22: 10uF; 0805-NO
C15, C16, C20, C21: 0.1uF; 0603-NO
FID1, FID2: FIDUCIAL_0.5MM
JP1: HEADER-1X870MIL; 1X08_ROUND_70
JP3: HEADER-1X1070MIL; 1X10_ROUND70
R1, R8, R9: 10k; 0603-NO
R3: 2.2K; 0603-NO
SJ1: SOLDERJUMPER_2WAY; SOLDERJUMPER_2WAY_OPEN_NOPASTE
U1: TLV320DAC3100
U2: AP2127K-3.3; SOT23-5
U3: AP2127K-1.8; SOT23-5
U$12, U$13, U$14: MOUNTINGHOLE2.5; MOUNTINGHOLE_2.5_PLATED
X1: CON_JST_PH_2PIN_MTPH2; JSTPH2
X3: TRRS_2SWITCH_PJ332A; PJ-332A

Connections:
1.8V: C4.1, C15.1, C16.1, U1.3 (DVDD), U3.5 (OUT)
3.3V: C12.1, C20.1, C21.1, C22.1, R1.2, R8.2, R9.2, U1.2 (IOVDD), U1.17 (AVDD), U1.28 (HPVDD), U2.5 (OUT)
!RESET: JP1.5, R1.1, U1.31 (!RESET)
AGND: C3.2, C4.2, C11.2, C12.2, C15.2, C16.2, C19.2, C20.2, C21.2, C22.2, JP3.2, SJ1.3, U1.1 (IOVSS), U1.16 (AVSS), U1.18 (DVSS), U1.20 (SPKVSS), U1.25 (SPKVSS), U1.29 (HPVSS), U1.33 (EP), U2.2 (GND), U3.2 (GND), X1.NC1, X1.NC2, X3.2 (RING1)
AIN1: JP1.2, U1.13 (AIN1)
AIN2: JP1.3, U1.14 (AIN2)
BITCLK_IN: JP3.7, U1.7 (BCLK)
DATA_IN: JP3.5, U1.5 (DIN)
GPIO1: JP1.4, U1.32 (GPIO1)
HPL: C1.1, U1.27 (HPL)
HPR: C2.1, U1.30 (HPR)
MCLK: JP3.8, U1.8 (MCLK)
MIC: JP1.8, R3.1, SJ1.2, X3.1 (RING)
MICBIAS: JP1.1, R3.2, U1.12 (MICBIAS)
MICDET: SJ1.1, U1.11 (VOL/MICDET)
OUTL: C1.2, JP1.7, X3.4 (TIP), X3.6 (TIP_SW)
OUTR: C2.2, JP1.6, X3.3 (RING2), X3.5 (R2_SW)
SCL: JP3.3, R9.1, U1.10 (SCL)
SDA: JP3.4, R8.1, U1.9 (SDA)
SPKM: JP3.9, U1.19 (SPKM), U1.23 (SPKM), X1.2
SPKP: JP3.10, U1.22 (SPKP), U1.26 (SPKP), X1.1
VIN: C3.1, C11.1, C19.1, JP3.1, U1.21 (SPKVDD), U1.24 (SPKVDD), U2.1 (IN), U2.3 (EN), U3.1 (IN), U3.3 (EN)
WORDSEL_IN: JP3.6, U1.6 (WCLK)

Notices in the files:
parts and their libraries:
microbuilder: This work is placed in the public domain, and may be freely used for commercial and non-commercial work with the following conditions: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
SparkFun: Licensing: CC v3.0 Share-Alike You are welcome to use this library for commercial purposes.
